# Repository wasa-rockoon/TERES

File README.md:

# Tiny & Extendable Rocket Electronics Stack

モデルロケットに搭載可能な，小型かつ拡張可能な電装

[テレメトリ・コマンド運用](https://wasa-rockoon.github.io/TERES/)

# 要求

- 内径40mmのボディに収まること
- 水密を確保できること
- ミッションや開発状況に応じて組み替え・拡張可能であること

# 仕様

- モジュール式
- マイコン：主にRP2040

## 外形

各モジュールは円盤状で，これを積み重ねて固定した上でロケットのボディ部またはノーズ部に搭載できる．

- 基板外径：36mm
- 基板間コネクタ：2.54mmピッチ ピンヘッダ・ピンソケット
- 固定：M2プラスチックスペーサーx4

## バス

上下のモジュールとUARTで通信し，デイジーチェーンで全体にわたるバスを形成する．

1. GND
2. UART TX
3. V+ (3.6V ~ 6V)
4. UART RX
5. GND

[通信プロトコル](https://github.com/wasa-rockoon/WCCP)

## モジュール

### LiPo電源

- 電源スイッチ
- 外部電源入力
- LiPo充電コントローラ
- LiPo温度センサ
- LiPoヒータ
- ハイサイド電流センサ

### GNSS

- GNSS受信モジュール
- バックアップ用充電池

### センサー

- 9軸センサ
- 気圧センサ
- 外部温度センサ

### テレメトリ

- TWELITE (2.4GHz)
- LoRaモジュール (920MHz)

### ロガー

- MicroSDカード
- Flash
- RTC
- バックアップ用充電池

### カメラ

- ESP32
- カメラモジュール
- マイク

## 詳細設定

### テレメトリ項目・サンプリングコード

1. ダウンリンク(10 Hz)
- GNSS
- LiPo電池残量・温度
- 気圧データ
- 9軸センサの値(姿勢を可視化するプログラムを作れたら)

2. SDカード
- 外部温度センサ(10 Hz)
- 9軸センサの値(姿勢を可視化するプログラムを作れなかったら)(10 Hz)
- カメラ映像
- マイク

### 動作モード

1. 待機フェーズ(重力加速度のみ)
2. 上昇フェーズ(垂直方向加速度>0になってから規定時間 or 気圧低下中)
3. 下降フェーズ(発射から規定時間経過後 or 気圧上昇中)
- パラシュート展開成功(垂直方向加速度==0)
- 弾道落下(ABS(垂直方向加速度)==10)
4. 着陸後フェーズ(気圧変動なし & ABS(加速度ベクトル)==10)

# ビルド

## Arduino

Arduino のライブラリディレクトリに，`software/Library/`のシンボリックリンク（またはコピー）を追加する．

# 使い方
## 動画を生成する
```
python script/make_movie.py "<連番画像フォルダのパス>"
```

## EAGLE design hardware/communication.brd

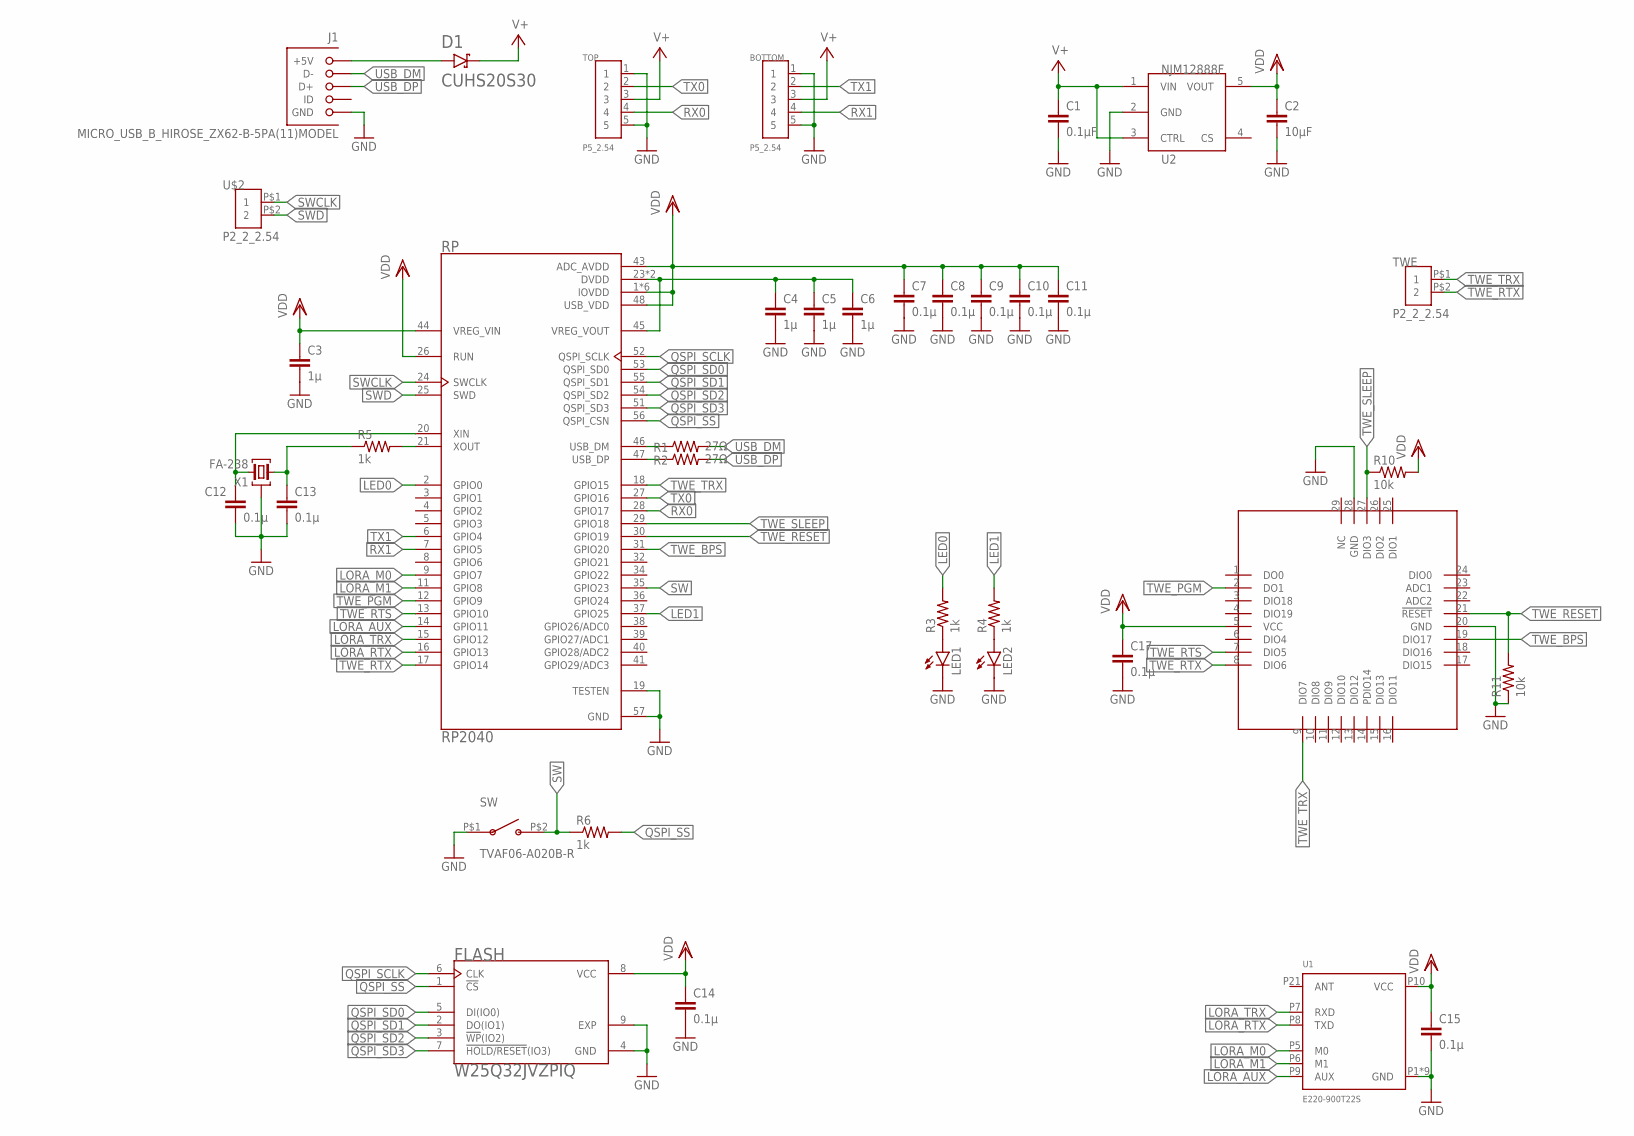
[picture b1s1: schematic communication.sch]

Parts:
BOTTOM: P5_2.54
C1: 0.1µF; C0402
C2: 10µF; C0402
C3, C4: 1µ; C0402
C5, C6: 1μ; C0402
C7, C8, C9, C10, C11, C15, C17: 0.1µ; C0402
C12, C13, C14: 0.1μ; C0402
D1: CUHS20S30
FLASH: W25Q32JVZPIQ; SON127P600X500X80-9N
J1: MICRO_USB_B_HIROSE_ZX62-B-5PA(11)MODEL; GHI-CONNECTORS_10118192-0001LF(MICRO-USB-B-AMPHENOL-FCI)
LED1, LED2: LEDCHIPLED_0603; CHIPLED_0603
R1, R2: 27Ω; R0402
R3, R4, R5, R6: 1k; R0402
R10, R11: 10k; R0402
RP: RP2040; QFN40P700X700X90-57N
SW: TVAF06-A020B-R
TOP: P5_2.54
TWE: P2_2_2.54; P2_2.54
U1: E220-900T22S
U2: NJM12888F; SOT95P240X110-5N
U$1: LITE
U$2: P2_2_2.54; P2_2.54
X1: FA-238

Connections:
1V2: C4.1, C5.1, C6.1, RP.23 (DVDD), RP.45 (VREG_VOUT), RP.50 (DVDD)
GND: BOTTOM.1, BOTTOM.5, C1.2, C2.2, C3.2, C4.2, C5.2, C6.2, C7.2, C8.2, C9.2, C10.2, C11.2, C12.2, C13.2, C14.2, C15.2, C17.2, FLASH.4 (GND), FLASH.9 (EXP), J1.CGND1 (GND), J1.CGND2 (GND), J1.CGND3 (GND), J1.CGND4 (GND), J1.CGND5 (GND), J1.CGND6 (GND), J1.GND, LED1.C, LED2.C, R11.1, RP.19 (TESTEN), RP.57 (GND), SW.P$1 (A), TOP.1, TOP.5, U1.P1 (GND), U1.P2 (GND), U1.P3 (GND), U1.P4 (GND), U1.P11 (GND), U1.P13 (GND), U1.P19 (GND), U1.P20 (GND), U1.P22 (GND), U2.2 (GND), U$1.20 (GND), U$1.28 (GND), X1.2 (G), X1.4 (G)
LED0: R3.2, RP.2 (GPIO0)
LED1: R4.2, RP.37 (GPIO25)
LORA_AUX: RP.14 (GPIO11), U1.P9 (AUX)
LORA_M0: RP.9 (GPIO7), U1.P5 (M0)
LORA_M1: RP.11 (GPIO8), U1.P6 (M1)
LORA_RTX: RP.16 (GPIO13), U1.P8 (TXD)
LORA_TRX: RP.15 (GPIO12), U1.P7 (RXD)
unnamed: D1.A, J1.VBUS (+5V)
unnamed: LED1.A, R3.1
unnamed: LED2.A, R4.1
unnamed: C13.1, R5.1, X1.1
QSPI_SCLK: FLASH.6 (CLK), RP.52 (QSPI_SCLK)
QSPI_SD0: FLASH.5 (DI(IO0)), RP.53 (QSPI_SD0)
QSPI_SD1: FLASH.2 (DO(IO1)), RP.55 (QSPI_SD1)
QSPI_SD2: FLASH.3 (!WP!(IO2)), RP.54 (QSPI_SD2)
QSPI_SD3: FLASH.7 (!HOLD/RESET!(IO3)), RP.51 (QSPI_SD3)
QSPI_SS: FLASH.1 (!CS), R6.2, RP.56 (QSPI_CSN)
RX0: RP.28 (GPIO17), TOP.4
RX1: BOTTOM.4, RP.7 (GPIO5)
SW: R6.1, RP.35 (GPIO23), SW.P$2 (B)
SWCLK: RP.24 (SWCLK), U$2.P$1 (1)
SWD: RP.25 (SWD), U$2.P$2 (2)
TWE_BPS: RP.31 (GPIO20), U$1.19 (DIO17)
TWE_PGM: RP.12 (GPIO9), U$1.2 (DO1)
TWE_RESET: R11.2, RP.30 (GPIO19), U$1.21 (!RESET!)
TWE_RTS: RP.13 (GPIO10), U$1.7 (DIO5)
TWE_RTX: RP.17 (GPIO14), TWE.P$2 (2), U$1.8 (DIO6)
TWE_SLEEP: R10.1, RP.29 (GPIO18), U$1.27 (DIO3)
TWE_TRX: RP.18 (GPIO15), TWE.P$1 (1), U$1.9 (DIO7)
TX0: RP.27 (GPIO16), TOP.2
TX1: BOTTOM.2, RP.6 (GPIO4)
USB_DM: J1.D-, R1.2
USB_DM_1: R1.1, RP.46 (USB_DM)
USB_DP: J1.D+, R2.2
USB_DP_1: R2.1, RP.47 (USB_DP)
V+: BOTTOM.3, C1.1, D1.C, TOP.3, U2.1 (VIN), U2.3 (CTRL)
VDD: C2.1, C3.1, C7.1, C8.1, C9.1, C10.1, C11.1, C14.1, C15.1, C17.1, FLASH.8 (VCC), R10.2, RP.1 (IOVDD), RP.10 (IOVDD), RP.22 (IOVDD), RP.26 (RUN), RP.33 (IOVDD), RP.42 (IOVDD), RP.43 (ADC_AVDD), RP.44 (VREG_VIN), RP.48 (USB_VDD), RP.49 (IOVDD), U1.P10 (VCC), U2.5 (VOUT), U$1.5 (VCC)
XIN1: C12.1, RP.20 (XIN), X1.3 (2)
XOUT1: R5.2, RP.21 (XOUT)

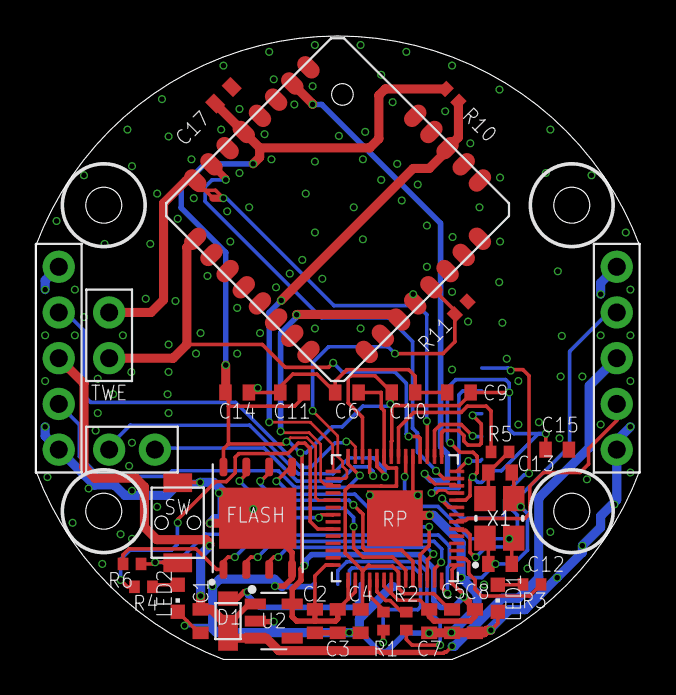
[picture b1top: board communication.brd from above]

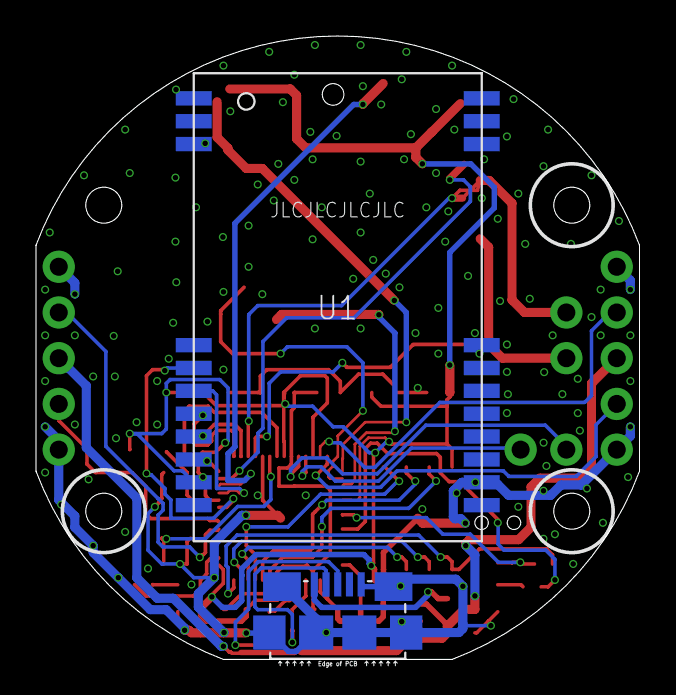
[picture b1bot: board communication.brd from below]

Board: 2 copper layers, 33.5 x 34.6 mm, 39 parts (2 on the bottom side), 41 nets.

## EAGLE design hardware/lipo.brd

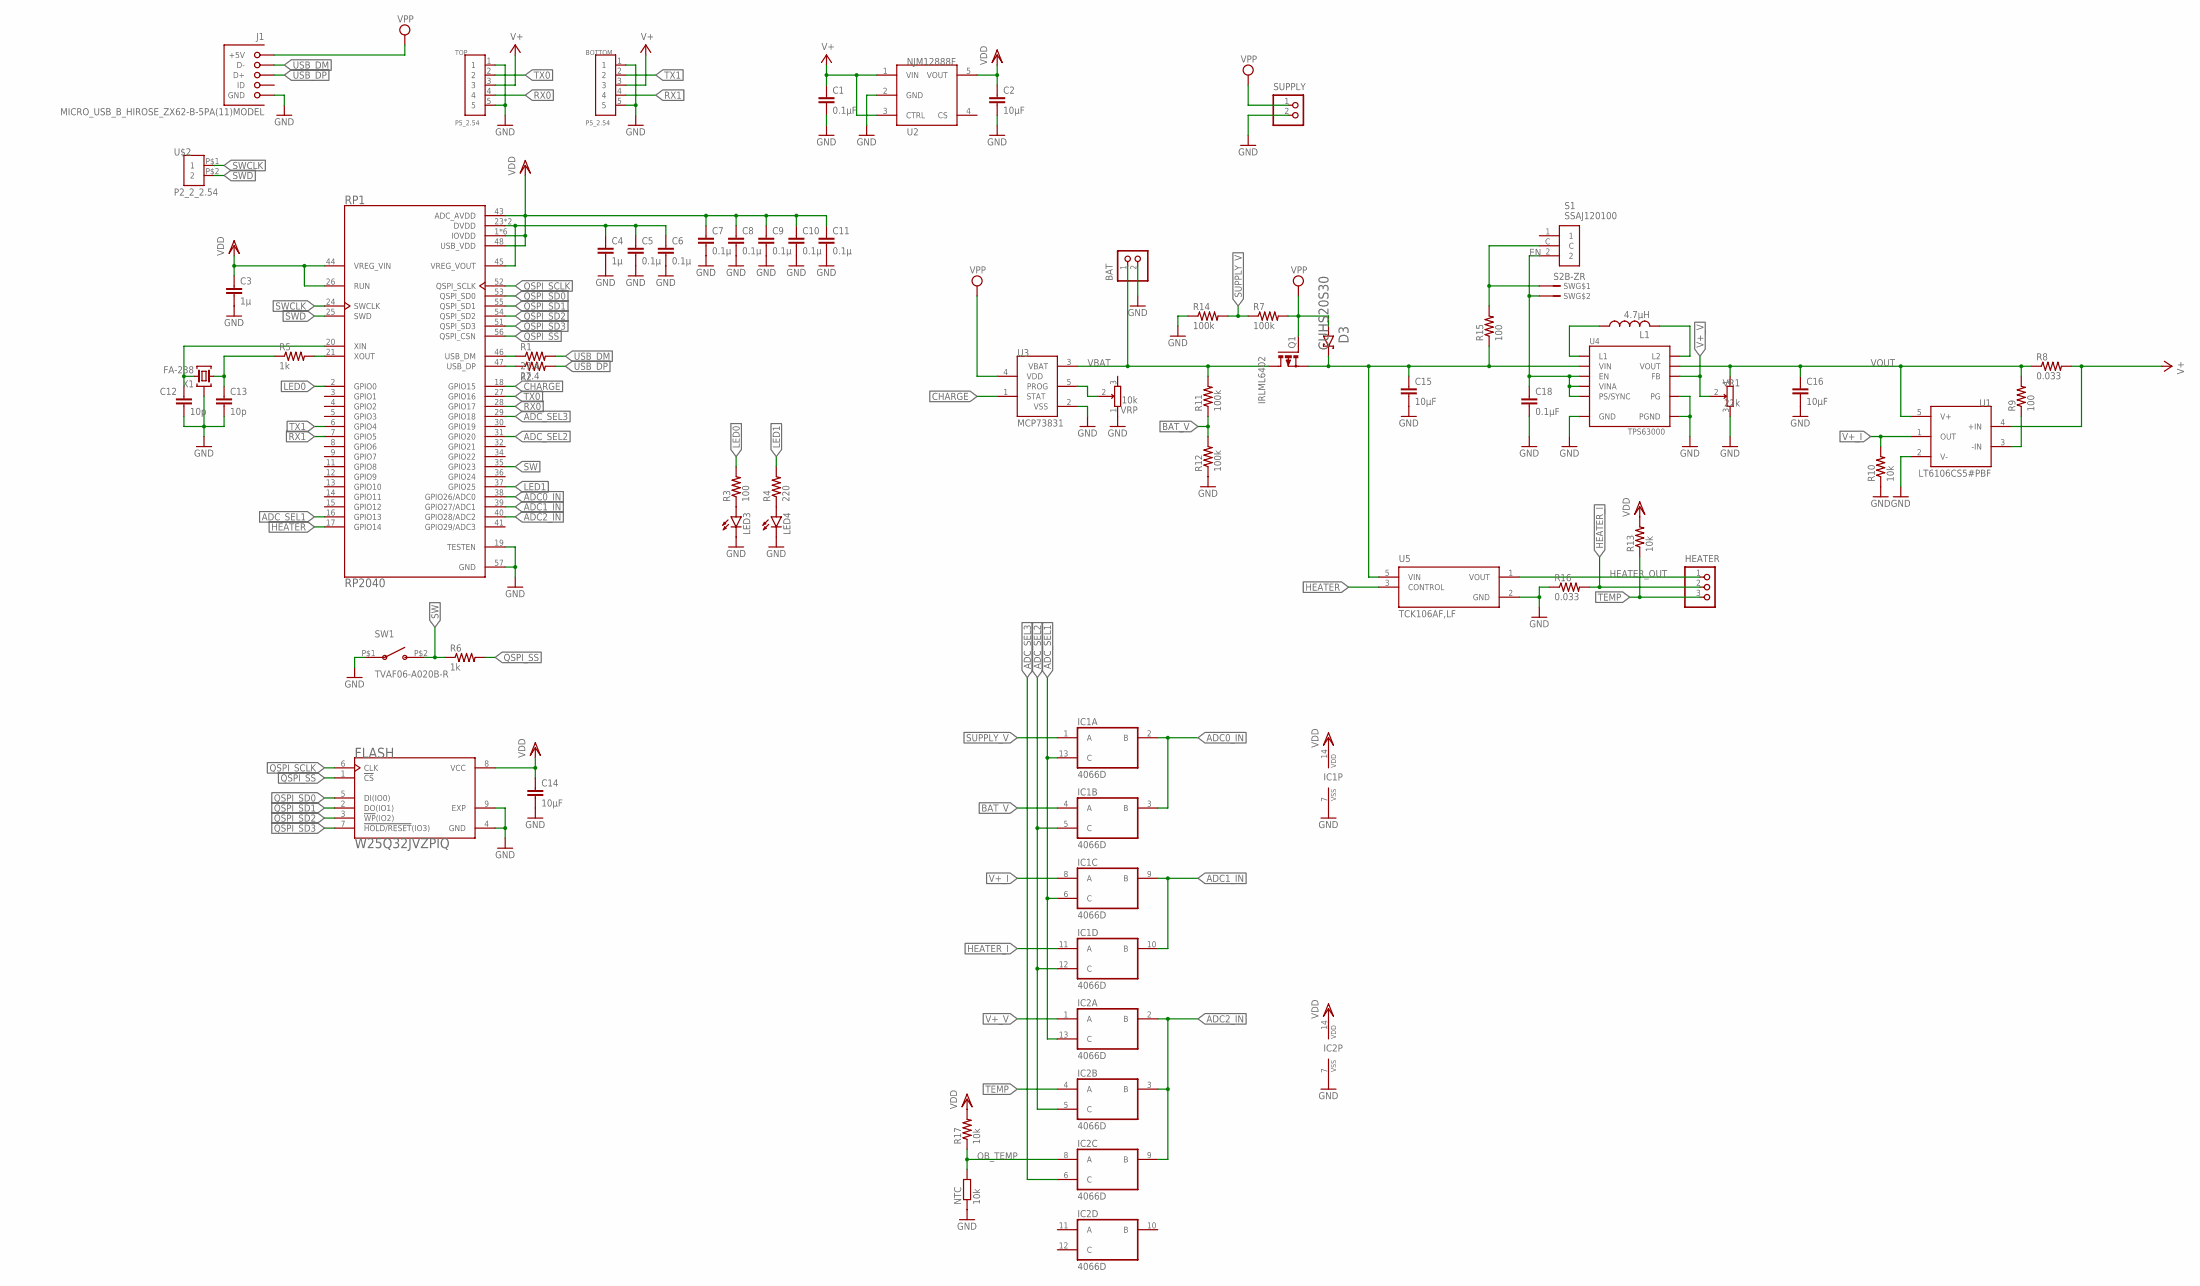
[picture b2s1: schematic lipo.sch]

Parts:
BAT: S2B-PH-K-S
BOTTOM: P5_2.54
C1, C18: 0.1µF; C0402
C2, C14, C15, C16: 10µF; C0402
C3, C4: 1µ; C0402
C5, C6, C7, C8, C9, C10, C11: 0.1µ; C0402
C12, C13: 10p; C0402
D3: CUHS20S30
FLASH: W25Q32JVZPIQ; SON127P600X500X80-9N
HEATER: S3B-PH-K-S
IC1, IC2: 4066D; SO14
J1: MICRO_USB_B_HIROSE_ZX62-B-5PA(11)MODEL; GHI-CONNECTORS_10118192-0001LF(MICRO-USB-B-AMPHENOL-FCI)
L1: 4.7µH; L3225M
LED3, LED4: LEDCHIPLED_0603; CHIPLED_0603
NTC: 10k; R0603
Q1: IRLML6402; SOT-23
R1, R2: 27.4; R0402
R3, R9, R15: 100; R0402
R4: 220; R0402
R5, R6: 1k; R0402
R7, R11, R12, R14: 100k; R0402
R8, R16: 0.033; R0603
R10, R13, R17: 10k; R0402
RP1: RP2040; QFN40P700X700X90-57N
S1: SSAJ120100
SUPPLY: S2B-PH-K-S
SW: S2B-ZR
SW1: TVAF06-A020B-R
TOP: P5_2.54
U1: LT6106CS5#PBF; SOT95P280X100-5N_LT6106CS5#PBF
U2: NJM12888F; SOT95P240X110-5N
U3: MCP73831; SOT23-5L
U4: TPS63000; 10-VFDFN
U5: TCK106AF,LF; IC_TCK106AF,LF
U$2: P2_2_2.54; P2_2.54
VR1: 22k; PVZ3A
VRP: 10k; PVZ3A
X1: FA-238

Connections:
1V2: C4.1, C5.1, C6.1, RP1.23 (DVDD), RP1.45 (VREG_VOUT), RP1.50 (DVDD)
ADC0_IN: IC1.2 (B), IC1.3 (B), RP1.38 (GPIO26/ADC0)
ADC1_IN: IC1.9 (B), IC1.10 (B), RP1.39 (GPIO27/ADC1)
ADC2_IN: IC2.2 (B), IC2.3 (B), IC2.9 (B), RP1.40 (GPIO28/ADC2)
ADC_SEL1: IC1.6 (C), IC1.13 (C), IC2.13 (C), RP1.16 (GPIO13)
ADC_SEL2: IC1.5 (C), IC1.12 (C), IC2.5 (C), RP1.31 (GPIO20)
ADC_SEL3: IC2.6 (C), RP1.29 (GPIO18)
BAT_V: IC1.4 (A), R11.1, R12.2
CHARGE: RP1.18 (GPIO15), U3.1 (STAT)
EN: C18.1, S1.2, SW.2, U4.6 (EN), U4.7 (PS/SYNC), U4.8 (VINA)
GND: BAT.2, BOTTOM.1, BOTTOM.5, C1.2, C2.2, C3.2, C4.2, C5.2, C6.2, C7.2, C8.2, C9.2, C10.2, C11.2, C12.2, C13.2, C14.2, C15.2, C16.2, C18.2, FLASH.4 (GND), FLASH.9 (EXP), IC1.7 (VSS), IC2.7 (VSS), J1.CGND1 (GND), J1.CGND2 (GND), J1.CGND3 (GND), J1.CGND4 (GND), J1.CGND5 (GND), J1.CGND6 (GND), J1.GND, LED3.C, LED4.C, NTC.1, R10.1, R12.1, R14.1, R16.1, RP1.19 (TESTEN), RP1.57 (GND), SUPPLY.2, SW1.P$1 (A), TOP.1, TOP.5, U1.2 (V-), U2.2 (GND), U3.2 (VSS), U4.3 (PGND), U4.9 (GND), U4.P$1 (PG), U4.P$2 (PG), U4.P$3 (PG), U4.P$4 (PG), U4.P$5 (PG), U5.2 (GND), VR1.3, VRP.1, X1.2 (G), X1.4 (G)
HEATER: RP1.17 (GPIO14), U5.3 (CONTROL)
HEATER_I: HEATER.2, IC1.11 (A), R16.2
HEATER_OUT: HEATER.1, U5.1 (VOUT)
LED0: R3.2, RP1.2 (GPIO0)
LED1: R4.2, RP1.37 (GPIO25)
unnamed: L1.1, U4.4 (L1)
unnamed: R9.1, U1.3 (-IN)
unnamed: U3.5 (PROG), VRP.2
unnamed: L1.2, U4.2 (L2)
unnamed: LED3.A, R3.1
unnamed: LED4.A, R4.1
unnamed: C13.1, R5.1, X1.1
unnamed: R15.2, S1.C, SW.1
OB_TEMP: IC2.8 (A), NTC.2, R17.1
QSPI_SCLK: FLASH.6 (CLK), RP1.52 (QSPI_SCLK)
QSPI_SD0: FLASH.5 (DI(IO0)), RP1.53 (QSPI_SD0)
QSPI_SD1: FLASH.2 (DO(IO1)), RP1.55 (QSPI_SD1)
QSPI_SD2: FLASH.3 (!WP!(IO2)), RP1.54 (QSPI_SD2)
QSPI_SD3: FLASH.7 (!HOLD/RESET!(IO3)), RP1.51 (QSPI_SD3)
QSPI_SS: FLASH.1 (!CS), R6.2, RP1.56 (QSPI_CSN)
RX0: RP1.28 (GPIO17), TOP.4
RX1: BOTTOM.4, RP1.7 (GPIO5)
SUPPLY_V: IC1.1 (A), R7.1, R14.2
SW: R6.1, RP1.35 (GPIO23), SW1.P$2 (B)
SWCLK: RP1.24 (SWCLK), U$2.P$1 (1)
SWD: RP1.25 (SWD), U$2.P$2 (2)
TEMP: HEATER.3, IC2.4 (A), R13.1
TX0: RP1.27 (GPIO16), TOP.2
TX1: BOTTOM.2, RP1.6 (GPIO4)
USB_DM: J1.D-, R1.2
USB_DM_1: R1.1, RP1.46 (USB_DM)
USB_DP: J1.D+, R2.2
USB_DP_1: R2.1, RP1.47 (USB_DP)
V+: BOTTOM.3, C1.1, R8.2, TOP.3, U1.4 (+IN), U2.1 (VIN), U2.3 (CTRL)
V+_I: IC1.8 (A), R10.2, U1.1 (OUT)
V+_V: IC2.1 (A), U4.10 (FB), VR1.2
VBAT: BAT.1, Q1.P3 (D), R11.2, U3.3 (VBAT)
VBAT_: C15.1, D3.C, Q1.P2 (S), R15.1, U4.5 (VIN), U5.5 (VIN)
VDD: C2.1, C3.1, C7.1, C8.1, C9.1, C10.1, C11.1, C14.1, FLASH.8 (VCC), IC1.14 (VDD), IC2.14 (VDD), R13.2, R17.2, RP1.1 (IOVDD), RP1.10 (IOVDD), RP1.22 (IOVDD), RP1.26 (RUN), RP1.33 (IOVDD), RP1.42 (IOVDD), RP1.43 (ADC_AVDD), RP1.44 (VREG_VIN), RP1.48 (USB_VDD), RP1.49 (IOVDD), U2.5 (VOUT)
VOUT: C16.1, R8.1, R9.2, U1.5 (V+), U4.1 (VOUT), VR1.1
VPP: D3.A, J1.VBUS (+5V), Q1.P1 (G), R7.2, SUPPLY.1, U3.4 (VDD)
XIN1: C12.1, RP1.20 (XIN), X1.3 (2)
XOUT1: R5.2, RP1.21 (XOUT)

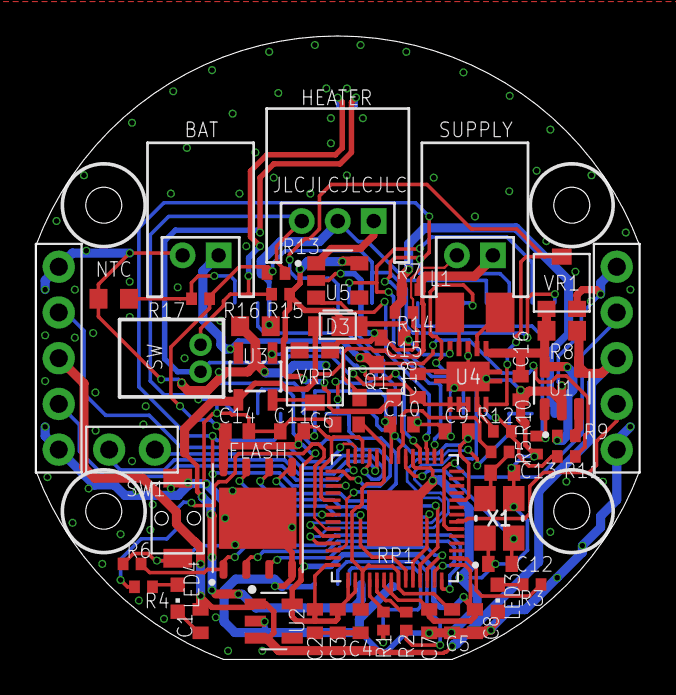
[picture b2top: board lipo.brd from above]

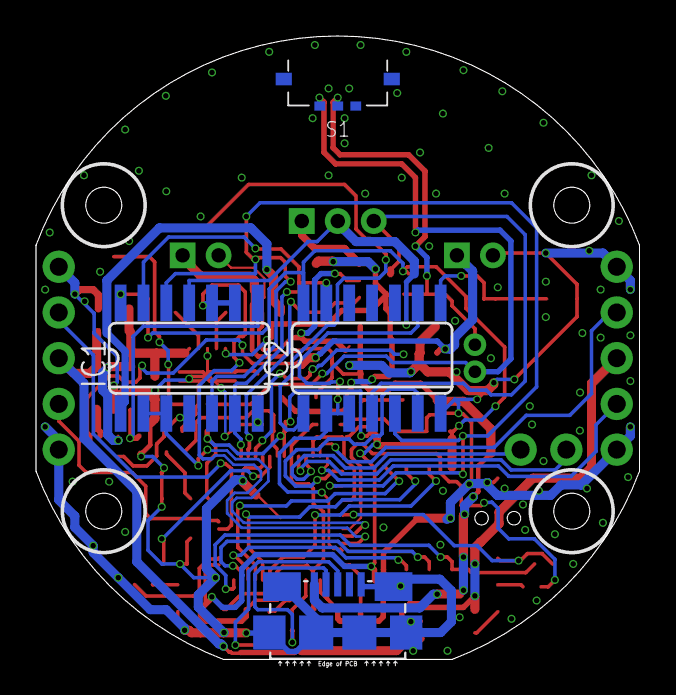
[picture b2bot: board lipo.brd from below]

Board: 2 copper layers, 33.5 x 34.6 mm, 62 parts (4 on the bottom side), 54 nets.

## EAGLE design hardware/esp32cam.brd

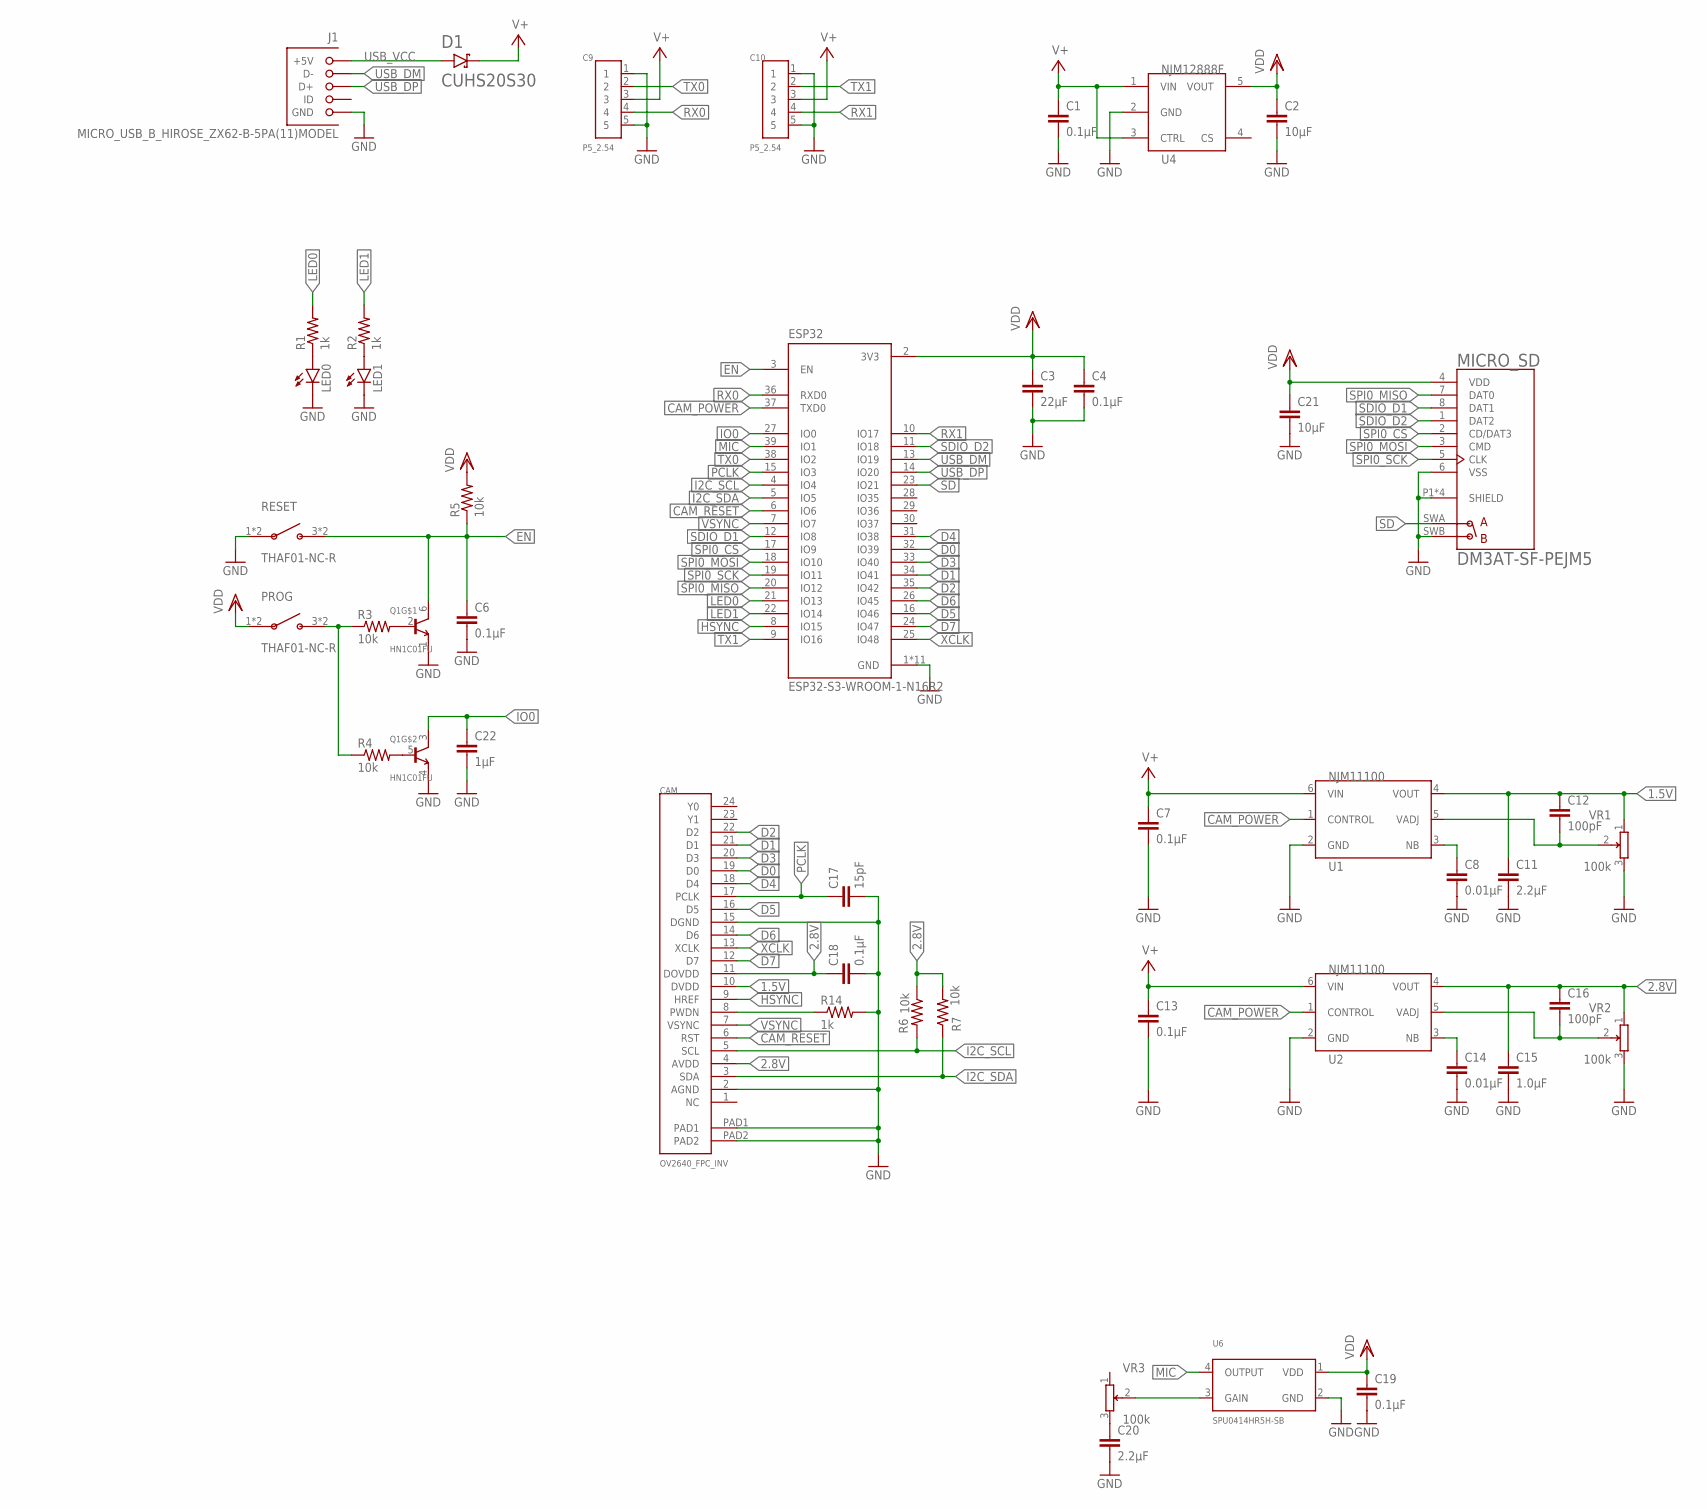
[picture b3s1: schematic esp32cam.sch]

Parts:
C1, C4, C6, C7, C13, C18, C19: 0.1µF; C0402
C2, C21: 10µF; C0402
C3: 22µF; C0402
C8, C14: 0.01µF; C0402
C9, C10: P5_2.54
C11, C20: 2.2µF; C0402
C12, C16: 100pF; C0402
C15: 1.0µF; C0402
C17: 15pF; C0402
C22: 1µF; C0402
CAM: OV2640_FPC_INV; FH12-24S-0.5SH
D1: CUHS20S30
ESP32: ESP32-S3-WROOM-1-N16R2; XCVR_ESP32-S3-WROOM-1-N16R2
J1: MICRO_USB_B_HIROSE_ZX62-B-5PA(11)MODEL; GHI-CONNECTORS_10118192-0001LF(MICRO-USB-B-AMPHENOL-FCI)
LED0, LED1: LEDCHIPLED_0603; CHIPLED_0603
MICRO_SD: DM3AT-SF-PEJM5; HRS_DM3AT-SF-PEJM5
PROG: THAF01-NC-R
Q1: HN1C01FU; SOT-363
R1, R2, R14: 1k; R0402
R3, R4, R5, R6, R7: 10k; R0402
RESET: THAF01-NC-R
U1, U2: NJM11100; SOT95P240X110-6N
U4: NJM12888F; SOT95P240X110-5N
U6: SPU0414HR5H-SB
VR1, VR2, VR3: 100k; PVZ3A

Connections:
1.5V: C11.1, C12.1, CAM.10 (DVDD), U1.4 (VOUT), VR1.1
2.8V: C15.1, C16.1, C18.1, CAM.4 (AVDD), CAM.11 (DOVDD), R6.1, R7.2, U2.4 (VOUT), VR2.1
CAM_POWER: ESP32.37 (TXD0), U1.1 (CONTROL), U2.1 (CONTROL)
CAM_RESET: CAM.6 (RST), ESP32.6 (IO6)
D0: CAM.19 (D0), ESP32.32 (IO39)
D1: CAM.21 (D1), ESP32.34 (IO41)
D2: CAM.22 (D2), ESP32.35 (IO42)
D3: CAM.20 (D3), ESP32.33 (IO40)
D4: CAM.18 (D4), ESP32.31 (IO38)
D5: CAM.16 (D5), ESP32.16 (IO46)
D6: CAM.14 (D6), ESP32.26 (IO45)
D7: CAM.12 (D7), ESP32.24 (IO47)
EN: C6.1, ESP32.3 (EN), Q1.6 (C), R5.1, RESET.3 (B), RESET.4 (B)
GND: C1.2, C2.2, C3.2, C4.2, C6.2, C7.2, C8.2, C9.1, C9.5, C10.1, C10.5, C11.2, C13.2, C14.2, C15.2, C17.2, C18.2, C19.2, C20.2, C21.2, C22.2, CAM.2 (AGND), CAM.15 (DGND), CAM.PAD1, CAM.PAD2, ESP32.1 (GND), ESP32.40 (GND), ESP32.41_1 (GND), ESP32.41_2 (GND), ESP32.41_3 (GND), ESP32.41_4 (GND), ESP32.41_5 (GND), ESP32.41_6 (GND), ESP32.41_7 (GND), ESP32.41_8 (GND), ESP32.41_9 (GND), J1.CGND1 (GND), J1.CGND2 (GND), J1.CGND3 (GND), J1.CGND4 (GND), J1.CGND5 (GND), J1.CGND6 (GND), J1.GND, LED0.C, LED1.C, MICRO_SD.6 (VSS), MICRO_SD.P1 (SHIELD), MICRO_SD.P2 (SHIELD), MICRO_SD.P3 (SHIELD), MICRO_SD.P4 (SHIELD), MICRO_SD.SWB (B), Q1.1 (E), Q1.4 (E), R14.2, RESET.1 (A), RESET.2 (A), U1.2 (GND), U2.2 (GND), U4.2 (GND), U6.2 (GND), VR1.3, VR2.3
HSYNC: CAM.9 (HREF), ESP32.8 (IO15)
I2C_SCL: CAM.5 (SCL), ESP32.4 (IO4), R6.2
I2C_SDA: CAM.3 (SDA), ESP32.5 (IO5), R7.1
IO0: C22.1, ESP32.27 (IO0), Q1.3 (C)
LED0: ESP32.21 (IO13), R1.2
LED1: ESP32.22 (IO14), R2.2
MIC: ESP32.39 (IO1), U6.4 (OUTPUT)
unnamed: C8.1, U1.3 (NB)
unnamed: C12.2, U1.5 (VADJ), VR1.2
unnamed: C14.1, U2.3 (NB)
unnamed: C16.2, U2.5 (VADJ), VR2.2
unnamed: PROG.3 (B), PROG.4 (B), R3.1, R4.1
unnamed: LED0.A, R1.1
unnamed: LED1.A, R2.1
unnamed: Q1.2 (B), R3.2
unnamed: CAM.8 (PWDN), R14.1
unnamed: Q1.5 (B), R4.2
unnamed: U6.3 (GAIN), VR3.2
unnamed: C20.1, VR3.3
PCLK: C17.1, CAM.17 (PCLK), ESP32.15 (IO3)
RX0: C9.4, ESP32.36 (RXD0)
RX1: C10.4, ESP32.10 (IO17)
SD: ESP32.23 (IO21), MICRO_SD.SWA (A)
SDIO_D1: ESP32.12 (IO8), MICRO_SD.8 (DAT1)
SDIO_D2: ESP32.11 (IO18), MICRO_SD.1 (DAT2)
SPI0_CS: ESP32.17 (IO9), MICRO_SD.2 (CD/DAT3)
SPI0_MISO: ESP32.20 (IO12), MICRO_SD.7 (DAT0)
SPI0_MOSI: ESP32.18 (IO10), MICRO_SD.3 (CMD)
SPI0_SCK: ESP32.19 (IO11), MICRO_SD.5 (CLK)
TX0: C9.2, ESP32.38 (IO2)
TX1: C10.2, ESP32.9 (IO16)
USB_DM: ESP32.13 (IO19), J1.D-
USB_DP: ESP32.14 (IO20), J1.D+
USB_VCC: D1.A, J1.VBUS (+5V)
V+: C1.1, C7.1, C9.3, C10.3, C13.1, D1.C, U1.6 (VIN), U2.6 (VIN), U4.1 (VIN), U4.3 (CTRL)
VDD: C2.1, C3.1, C4.1, C19.1, C21.1, ESP32.2 (3V3), MICRO_SD.4 (VDD), PROG.1 (A), PROG.2 (A), R5.2, U4.5 (VOUT), U6.1 (VDD)
VSYNC: CAM.7 (VSYNC), ESP32.7 (IO7)
XCLK: CAM.13 (XCLK), ESP32.25 (IO48)

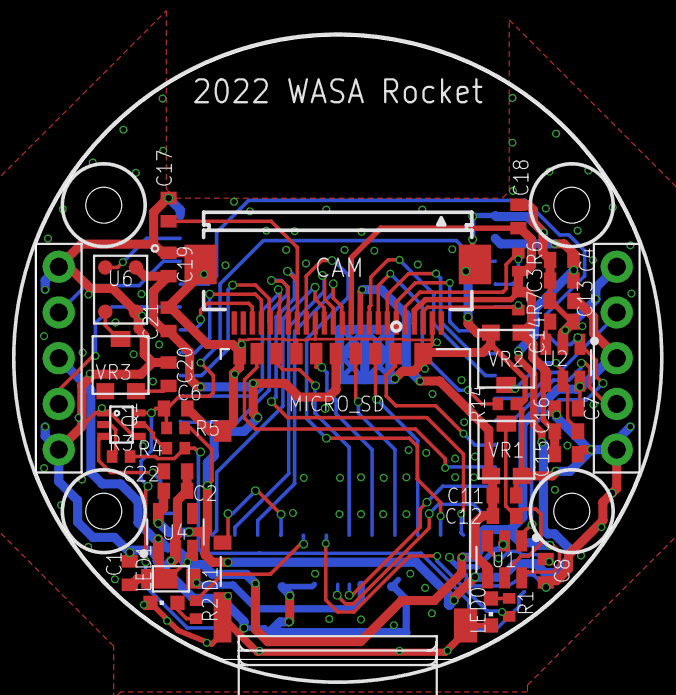
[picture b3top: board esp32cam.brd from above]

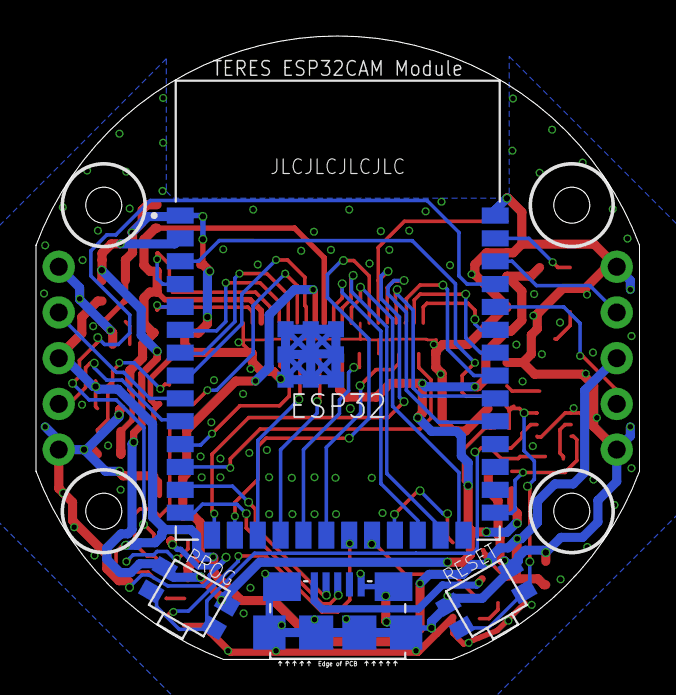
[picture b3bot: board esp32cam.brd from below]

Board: 2 copper layers, 33.5 x 34.6 mm, 46 parts (4 on the bottom side), 52 nets.

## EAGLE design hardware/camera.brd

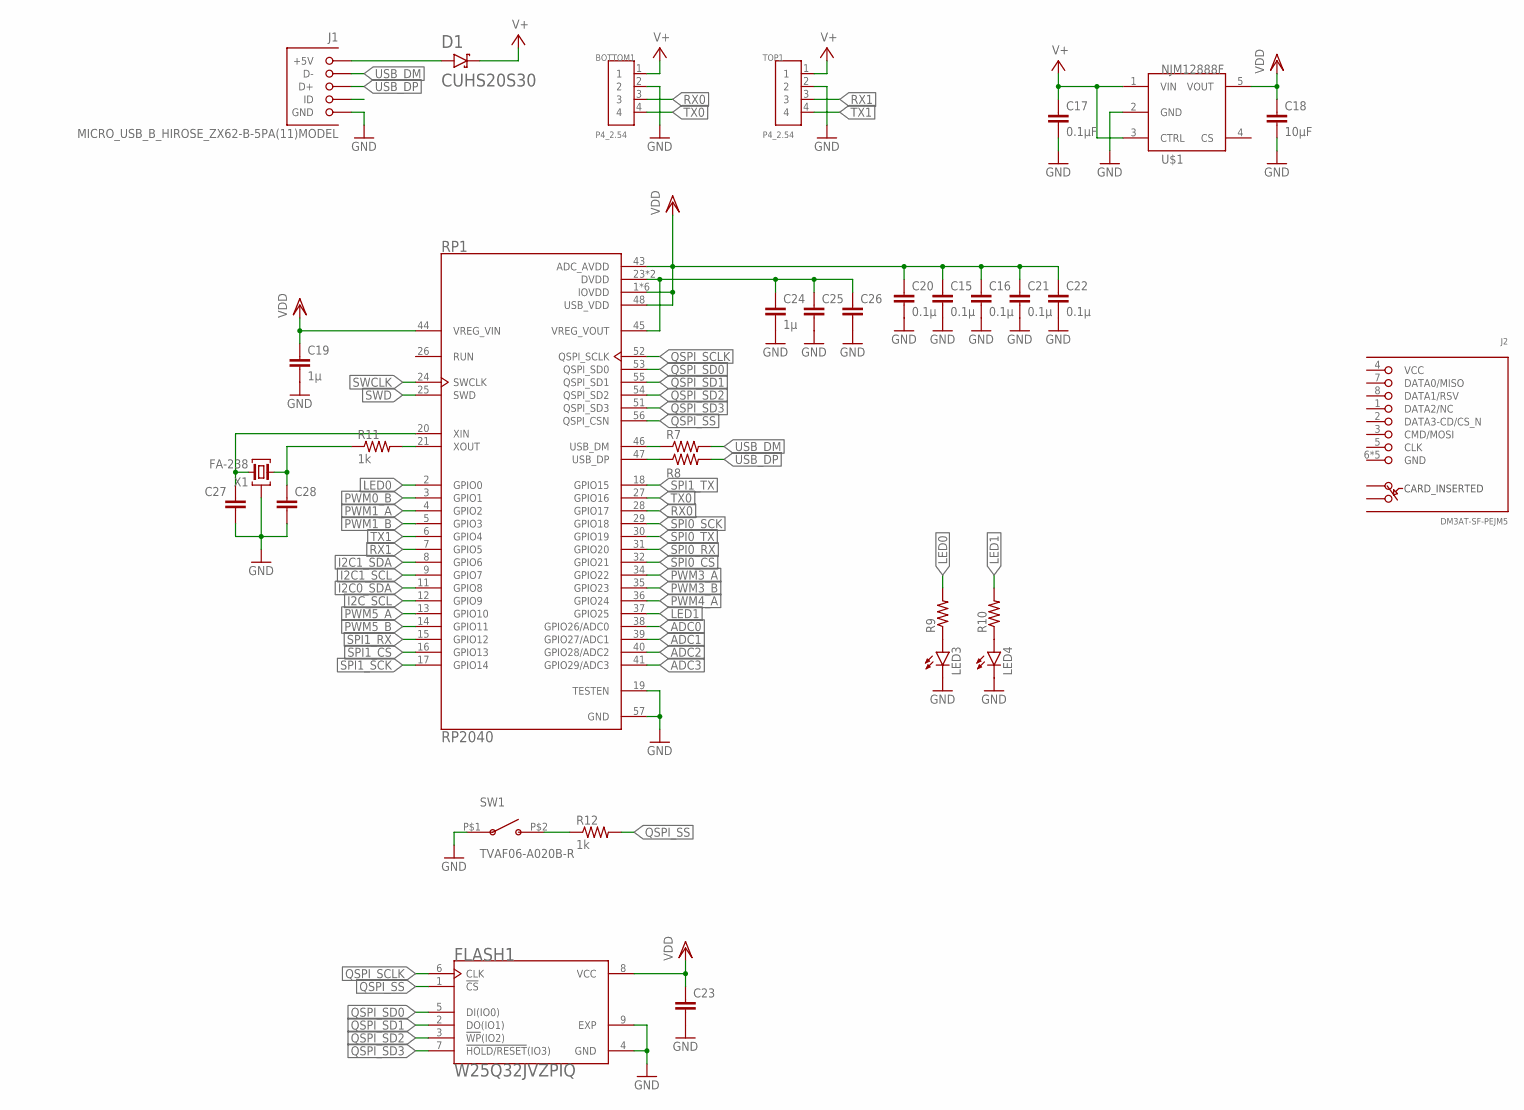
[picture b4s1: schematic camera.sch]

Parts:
BOTTOM1: P4_2.54
C15, C16, C20, C21, C22: 0.1µ; C0402
C17: 0.1µF; C0402
C18: 10µF; C0402
C19, C24: 1µ; C0402
C23, C25, C26, C27, C28: C-EUC0402; C0402
D1: CUHS20S30
FLASH1: W25Q32JVZPIQ; SON127P600X500X80-9N
J1: MICRO_USB_B_HIROSE_ZX62-B-5PA(11)MODEL; GHI-CONNECTORS_10118192-0001LF(MICRO-USB-B-AMPHENOL-FCI)
J2: DM3AT-SF-PEJM5
LED3, LED4: LEDCHIPLED_0603; CHIPLED_0603
R7, R8, R9, R10: R-US_R0402; R0402
R11, R12: 1k; R0402
RP1: RP2040; QFN40P700X700X90-57N
SW1: TVAF06-A020B-R
TOP1: P4_2.54
U$1: NJM12888F; SOT95P240X110-5N
X1: FA-238

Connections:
1V2: C24.1, C25.1, C26.1, RP1.23 (DVDD), RP1.45 (VREG_VOUT), RP1.50 (DVDD)
ADC0: RP1.38 (GPIO26/ADC0)
ADC1: RP1.39 (GPIO27/ADC1)
ADC2: RP1.40 (GPIO28/ADC2)
ADC3: RP1.41 (GPIO29/ADC3)
GND: BOTTOM1.2, C15.2, C16.2, C17.2, C18.2, C19.2, C20.2, C21.2, C22.2, C23.2, C24.2, C25.2, C26.2, C27.2, C28.2, FLASH1.4 (GND), FLASH1.9 (EXP), J1.CGND1 (GND), J1.CGND2 (GND), J1.CGND3 (GND), J1.CGND4 (GND), J1.CGND5 (GND), J1.CGND6 (GND), J1.GND, LED3.C, LED4.C, RP1.19 (TESTEN), RP1.57 (GND), SW1.P$1 (A), TOP1.2, U$1.2 (GND), X1.2 (G), X1.4 (G)
I2C0_SDA: RP1.11 (GPIO8)
I2C1_SCL: RP1.9 (GPIO7)
I2C1_SDA: RP1.8 (GPIO6)
I2C_SCL: RP1.12 (GPIO9)
LED0: R9.2, RP1.2 (GPIO0)
LED1: R10.2, RP1.37 (GPIO25)
unnamed: D1.A, J1.VBUS (+5V)
unnamed: LED3.A, R9.1
unnamed: LED4.A, R10.1
unnamed: C28.1, R11.1, X1.1
unnamed: R12.1, SW1.P$2 (B)
PWM0_B: RP1.3 (GPIO1)
PWM1_A: RP1.4 (GPIO2)
PWM1_B: RP1.5 (GPIO3)
PWM3_A: RP1.34 (GPIO22)
PWM3_B: RP1.35 (GPIO23)
PWM4_A: RP1.36 (GPIO24)
PWM5_A: RP1.13 (GPIO10)
PWM5_B: RP1.14 (GPIO11)
QSPI_SCLK: FLASH1.6 (CLK), RP1.52 (QSPI_SCLK)
QSPI_SD0: FLASH1.5 (DI(IO0)), RP1.53 (QSPI_SD0)
QSPI_SD1: FLASH1.2 (DO(IO1)), RP1.55 (QSPI_SD1)
QSPI_SD2: FLASH1.3 (!WP!(IO2)), RP1.54 (QSPI_SD2)
QSPI_SD3: FLASH1.7 (!HOLD/RESET!(IO3)), RP1.51 (QSPI_SD3)
QSPI_SS: FLASH1.1 (!CS), R12.2, RP1.56 (QSPI_CSN)
RX0: BOTTOM1.3, RP1.28 (GPIO17)
RX1: RP1.7 (GPIO5), TOP1.3
SPI0_CS: RP1.32 (GPIO21)
SPI0_RX: RP1.31 (GPIO20)
SPI0_SCK: RP1.29 (GPIO18)
SPI0_TX: RP1.30 (GPIO19)
SPI1_CS: RP1.16 (GPIO13)
SPI1_RX: RP1.15 (GPIO12)
SPI1_SCK: RP1.17 (GPIO14)
SPI1_TX: RP1.18 (GPIO15)
SWCLK: RP1.24 (SWCLK)
SWD: RP1.25 (SWD)
TX0: BOTTOM1.4, RP1.27 (GPIO16)
TX1: RP1.6 (GPIO4), TOP1.4
USB_DM: J1.D-, R7.2
USB_DM_1: R7.1, RP1.46 (USB_DM)
USB_DP: J1.D+, R8.2
USB_DP_1: R8.1, RP1.47 (USB_DP)
V+: BOTTOM1.1, C17.1, D1.C, TOP1.1, U$1.1 (VIN), U$1.3 (CTRL)
VDD: C15.1, C16.1, C18.1, C19.1, C20.1, C21.1, C22.1, C23.1, FLASH1.8 (VCC), RP1.1 (IOVDD), RP1.10 (IOVDD), RP1.22 (IOVDD), RP1.33 (IOVDD), RP1.42 (IOVDD), RP1.43 (ADC_AVDD), RP1.44 (VREG_VIN), RP1.48 (USB_VDD), RP1.49 (IOVDD), U$1.5 (VOUT)
XIN1: C27.1, RP1.20 (XIN), X1.3 (2)
XOUT1: R11.2, RP1.21 (XOUT)

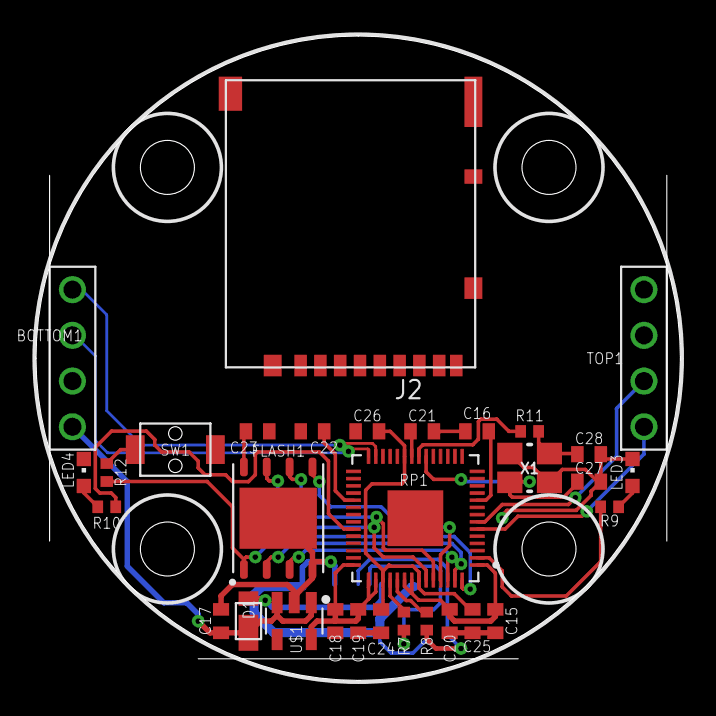
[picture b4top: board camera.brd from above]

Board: 2 copper layers, 35.8 x 35.8 mm, 32 parts (1 on the bottom side), 27 nets.

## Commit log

2022-10-04 Init
2022-11-01 Update spec
2022-12-02 communicationの回路図と基盤の途中経過です。Lo-Raの部分が終わって、残りはTweLiteをやれば完成のはずです。初めて基盤の設計をしているので不備が必ずあると思います。確認お願いします。
2022-12-08 communicationの層が一応完成しました。確認お願いします
2022-12-08 Revert "communicationの層が一応完成しました。確認お願いします"
    This reverts commit c7c23561daafb7c0ad8373af90d18b3355d51587.
2022-12-15 communication 回路図、基盤 更新
2022-12-15 communication基盤一部改良、GNSS基盤
2022-12-15 変更点: communication_LoRaをUART接続に変換 gnss_GPSのRTX接続およびRESETの追加
2022-12-21 loggerの基盤終わりました！
2022-12-30 センサーの基盤完了しました。エラー処理とか諸々終わってないので年末年始で頑張ります。抵抗値とかなにも入力してなかったのでしばらくかかりそうです。
2023-01-16 べたGND前です。esp32のschはノータッチなのでここに上がってないです。よろしくお願いします。
2023-01-16 LiPoのだけできなかったのですが、それ以外のべたGND済のものです。
2023-01-16 LoRa ResetとTWELITE TX&RXの引き出しピンを追加
2023-01-16 シルクを調整
2023-01-16 esp32cam途中
2023-01-17 変更点:カメラモジュール・SDカード・LED1,2接続、未接続だったVDD、GNDの接続 一応完成したはずです。確認お願いします。
2023-01-17 若干修正
2023-01-17 ステンシルを追加
2023-02-04 Update README.md
    詳細設定書き込みたいのでテストです
2023-02-04 Update README.md
    詳細設定自分なりに考えてみました。評価お願いします。
2023-02-12 プログラムの雛形を追加
2023-02-14 SDカード書き込みテスト
2023-02-18 I2Cテスト
2023-02-23 共通部分（バス，LED）
2023-02-25 ログ書き込み，バス通信
2023-02-26 TWELITE通信
2023-02-26 カメラコードの追加です。
2023-02-26 センサー完成
2023-02-26 バス不具合修正
2023-02-26 ロゴを追加
2023-02-27 連番画像から動画を作成するスクリプトを追加
2023-02-28 地上局を追加
2023-02-28 delay追加
2023-03-03 起動時から動作するように&SDのフォルダ内にファイルが増えすぎると遅くなるので1分ごとに分けるようにした
2023-03-03 バス処理とメイン処理を並列化
2023-03-03 SDのログの読み込み
2023-03-03 地上局からのテレメを非表示に
2023-03-03 並列化は無しで
2023-03-03 緯度経度のデコードを追加
2023-03-03 GPS座標のプロット
2023-03-03 GPS座標のプロット（修正）
2023-03-04 CSV出力を追加
2023-04-05 テレメトリ画面を追加
2023-04-06 Add fetching packets
2023-04-07 Add datastore
2023-04-09 パケットの表示を実装
2023-04-09 パケットを送信元別に表示
2023-04-09 図を追加
2023-04-10 図の描画範囲を変更可能に
2023-04-11 再生コントロールを追加
2023-04-12 地図を追加
2023-04-15 動画再生を実装
2023-04-15 警告表示を追加
2023-04-16 develop最新
2023-04-16 Merge
2023-04-16 Actions設定
2023-04-16 deploy: 7c46228cdda42b3b950a2d1a74288208ed71509b
2023-04-16 ビルド先を相対パスに
2023-04-16 deploy: 22be0a87f07613a86c39e4dd2f09302d41f677ff
2023-04-22 画像を追加
2023-04-22 deploy: d00d9c63c5c0ea15792ca2fa3e99621b39c1b833
2023-04-22 ルーターを修正
2023-04-22 deploy: 15161e72fadb031e9e135593a154c42fc3222b56
2023-04-22 404リダイレクトを追加
2023-04-22 deploy: f4851156326c2c717e03e1cc0f338955c61b0a5f
2023-05-07 LiPo回路修正，新LoRa
2023-05-07 アナログ入力を修正
2023-05-23 ブランチテスト(ほとんど変更していません)
2023-05-24 issue#5:TELES/communication 基盤設計完了したので確認お願いします。
2023-05-24 communication_修正
2023-05-25 LiPoモジュールの基板設計です。
2023-05-27 回路微修正
2023-05-27 ベタ・シルク調整
2024-02-29 deploy: 8b5a9dd54ff0e4e7bfa29dc1c756624ee06d9a8c
